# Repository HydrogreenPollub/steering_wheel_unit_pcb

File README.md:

View this project on [CADLAB.io](https://cadlab.io/project/29096). 

# steering_wheel_unit_pcb

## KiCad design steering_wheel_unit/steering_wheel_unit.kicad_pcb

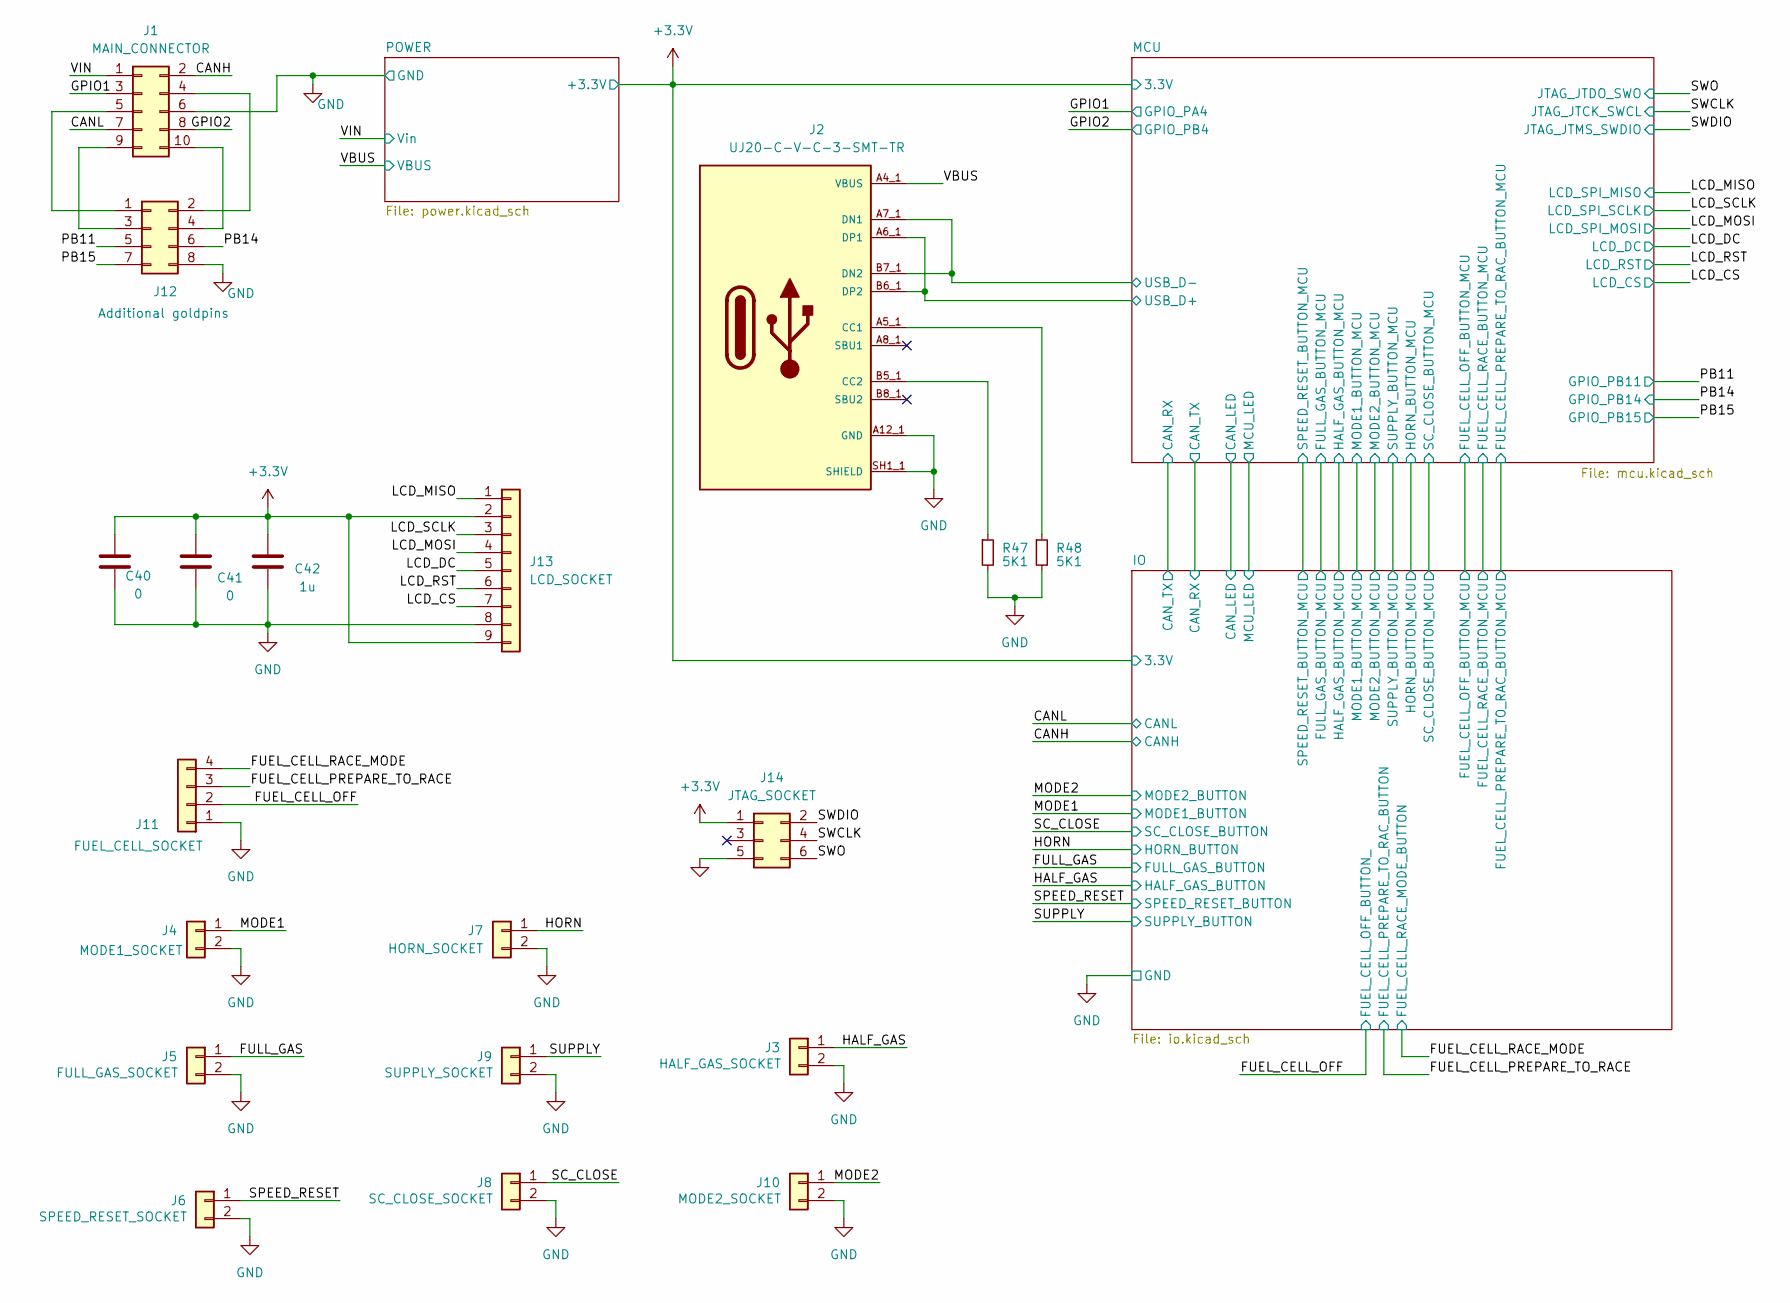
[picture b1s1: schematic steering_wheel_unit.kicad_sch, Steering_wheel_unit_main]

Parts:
C40, C41: 0; C_1206_3216Metric
C42: 1u; C_1206_3216Metric
J1: MAIN_CONNECTOR; MOLEX_39281103
J2: UJ20-C-V-C-3-SMT-TR; CUI_UJ20-C-V-C-3-SMT-TR; PARTREV 1.0
J3: HALF_GAS_SOCKET; JST_PH_B2B-PH-K_1x02_P2.00mm_Vertical
J4: MODE1_SOCKET; JST_PH_B2B-PH-K_1x02_P2.00mm_Vertical
J5: FULL_GAS_SOCKET; JST_PH_B2B-PH-K_1x02_P2.00mm_Vertical
J6: SPEED_RESET_SOCKET; JST_PH_B2B-PH-K_1x02_P2.00mm_Vertical
J7: HORN_SOCKET; JST_PH_B2B-PH-K_1x02_P2.00mm_Vertical
J8: SC_CLOSE_SOCKET; JST_PH_B2B-PH-K_1x02_P2.00mm_Vertical
J9: SUPPLY_SOCKET; JST_PH_B2B-PH-K_1x02_P2.00mm_Vertical
J10: MODE2_SOCKET; JST_PH_B2B-PH-K_1x02_P2.00mm_Vertical
J11: FUEL_CELL_SOCKET; JST_PH_B4B-PH-K_1x04_P2.00mm_Vertical
J12: Additional goldpins; PinHeader_2x04_P2.54mm_Vertical
J13: LCD_SOCKET; JST_PH_B9B-PH-K_1x09_P2.00mm_Vertical
J14: JTAG_SOCKET; IDC-Header_2x03_P2.54mm_Vertical
R47, R48: 5K1; R_1206_3216Metric

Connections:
+12V: J1.1; also elsewhere on the board
/CANH: J1.2; also elsewhere on the board
/CANL: J1.7; also elsewhere on the board
/FUEL_CELL_OFF: J11.2; also elsewhere on the board
/FUEL_CELL_PREPARE_TO_RACE: J11.3; also elsewhere on the board
/FUEL_CELL_RACE_MODE: J11.4; also elsewhere on the board
/FULL_GAS: J5.1; also elsewhere on the board
/GPIO1: J1.3; also elsewhere on the board
/GPIO2: J1.8; also elsewhere on the board
/HALF_GAS: J3.1; also elsewhere on the board
/HORN: J7.1; also elsewhere on the board
/LCD_CS: J14.7; also elsewhere on the board
/LCD_MOSI: J14.4; also elsewhere on the board
/LCD_RST: J14.6; also elsewhere on the board
/LCD_SCLK: J14.3; also elsewhere on the board
/MCU/USB_D+: J2.A6_1 (DP1), J2.A6_2 (DP1), J2.B6_1 (DP2), J2.B6_2 (DP2); also elsewhere on the board
/MCU/USB_D-: J2.A7_1 (DN1), J2.A7_2 (DN1), J2.B7_1 (DN2), J2.B7_2 (DN2); also elsewhere on the board
/MODE1: J4.1; also elsewhere on the board
/MODE2: J10.1; also elsewhere on the board
/PB11: J12.5; also elsewhere on the board
/PB14: J12.6; also elsewhere on the board
/PB15: J12.7; also elsewhere on the board
/SC_CLOSE: J8.1; also elsewhere on the board
/SPEED_RESET: J6.1; also elsewhere on the board
/SUPPLY: J9.1; also elsewhere on the board
/VBUS: J2.A4_1 (VBUS), J2.A4_2 (VBUS), J2.A9_1 (VBUS), J2.A9_2 (VBUS), J2.B4_1 (VBUS), J2.B4_2 (VBUS), J2.B9_1 (VBUS), J2.B9_2 (VBUS); also elsewhere on the board
unnamed: J1.4, J12.2
unnamed: J1.5, J12.1
unnamed: J1.9, J12.3
unnamed: J1.10, J12.4
unnamed: J2.A5_1 (CC1), J2.A5_2 (CC1), R48.1
unnamed: J2.B5_1 (CC2), J2.B5_2 (CC2), R47.1

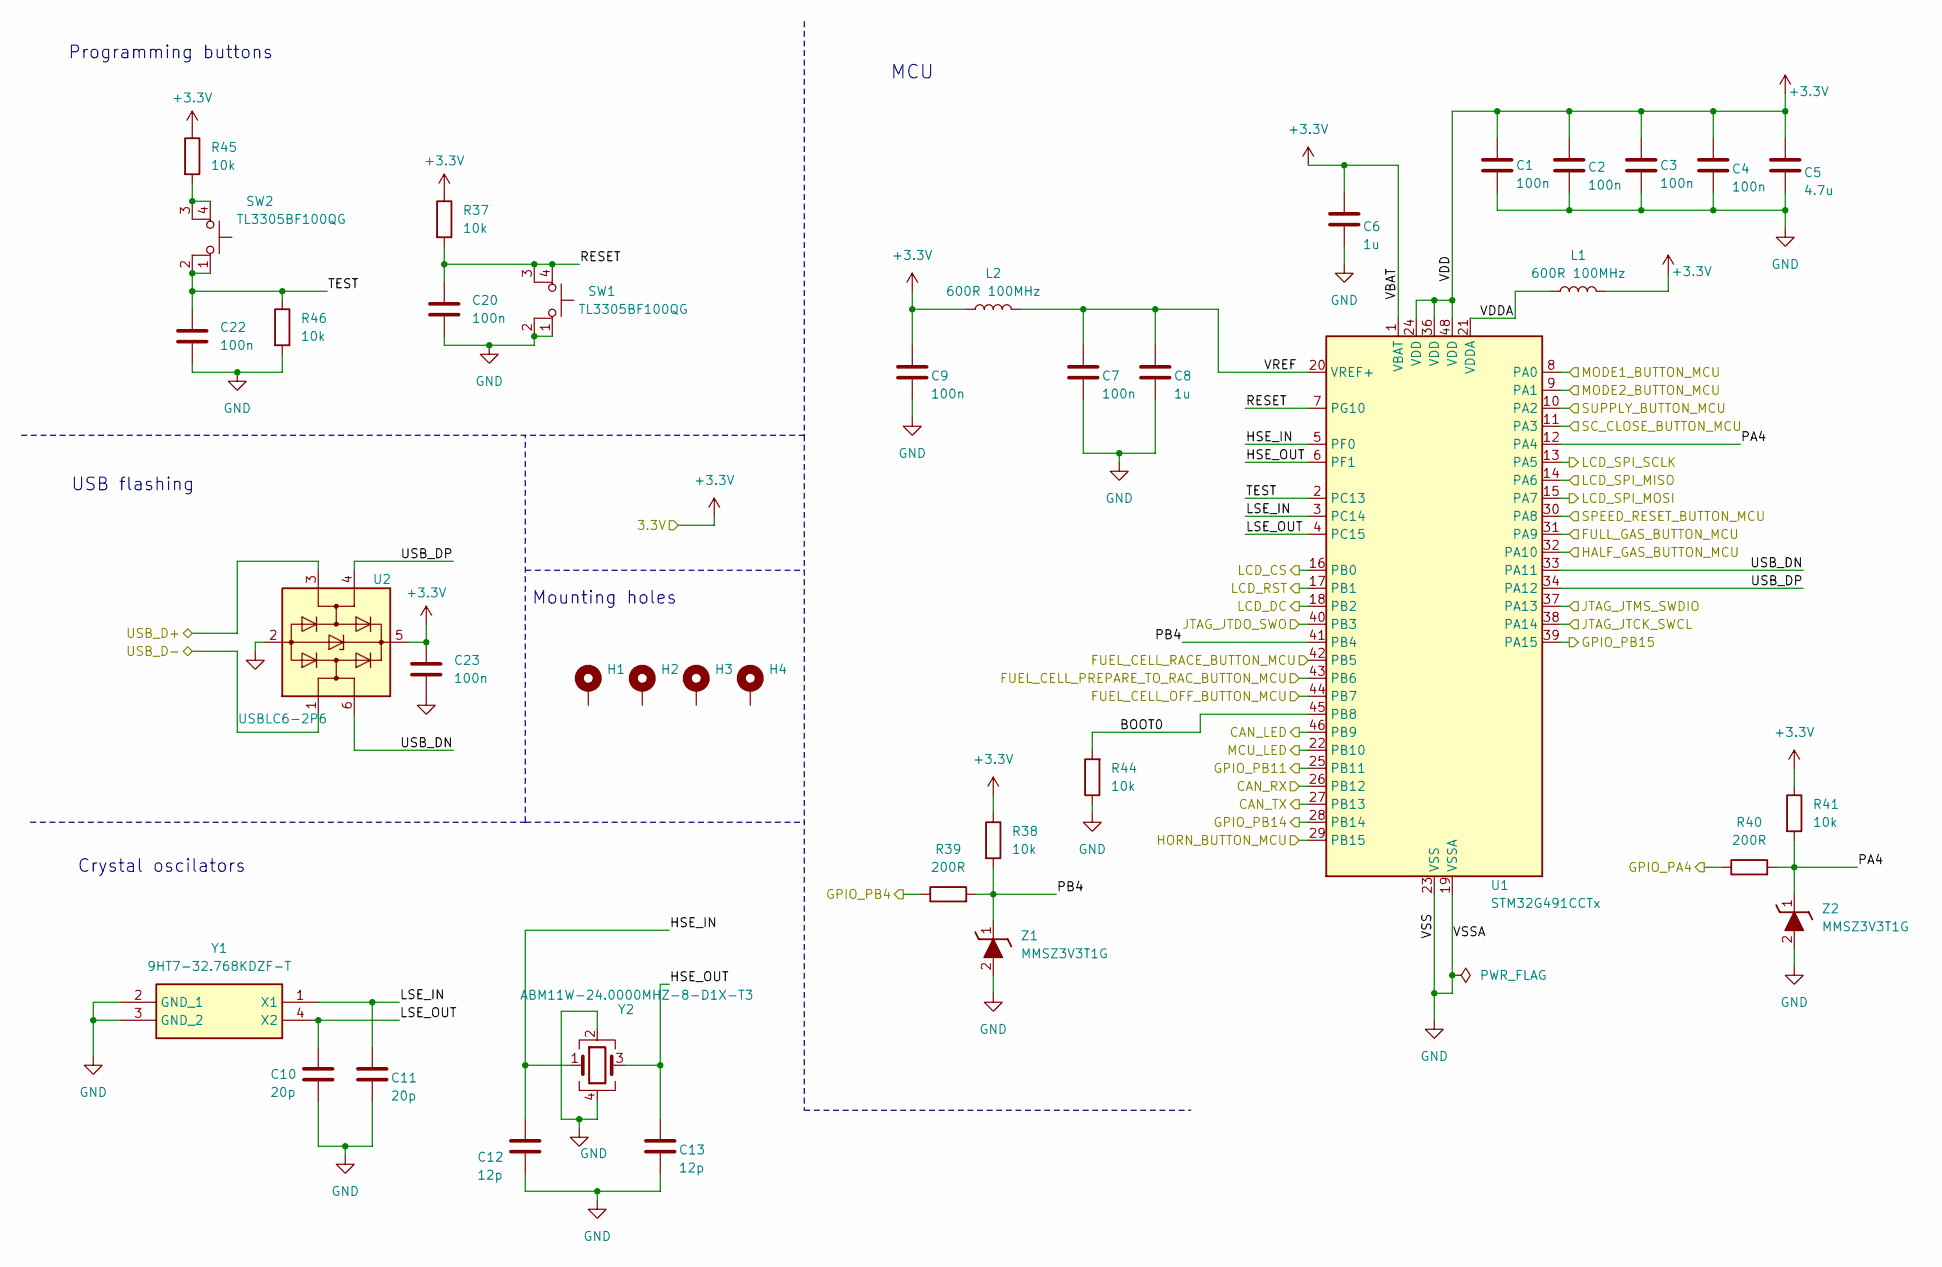
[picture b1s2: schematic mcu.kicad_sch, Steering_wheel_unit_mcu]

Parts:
C1, C2, C3, C4, C7, C9, C20, C22, C23: 100n; C_1206_3216Metric
C5: 4.7u; C_1206_3216Metric
C6, C8: 1u; C_1206_3216Metric
C10, C11: 20p; C_1206_3216Metric
C12, C13: 12p; C_1206_3216Metric
H1, H2, H3, H4: MountingHole_Pad; MountingHole_3.2mm_M3_Pad
L1, L2: 600R 100MHz; INDC1608X95N
R37, R38, R41, R44, R45, R46: 10k; R_1206_3216Metric
R39, R40: 200R; R_1206_3216Metric
SW1, SW2: TL3305BF100QG; SW_TL3305BF160QG; Mouser Part Number 612-TL3305BF100QG
U1: STM32G491CCTx; LQFP-48_7x7mm_P0.5mm
U2: USBLC6-2P6; SOT-666
Y1: 9HT7-32.768KDZF-T; 9HT732768KDZFT; Mouser Part Number 717-9HT7-32.768KDZFT
Y2: ABM11W-24.0000MHZ-8-D1X-T3; XTAL_ABM11W-24.0000MHZ-8-D1X-T3
Z1, Z2: MMSZ3V3T1G; SOD3716X135N; Mouser Part Number 863-MMSZ3V3T1G

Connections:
/GPIO1: R40.1; also elsewhere on the board
/GPIO2: R39.1; also elsewhere on the board
/IO/CAN_LED: U1.46 (PB9); also elsewhere on the board
/IO/CAN_RX: U1.27 (PB13); also elsewhere on the board
/IO/CAN_TX: U1.26 (PB12); also elsewhere on the board
/IO/FUEL_CELL_OFF_BUTTON_MCU: U1.44 (PB7); also elsewhere on the board
/IO/FUEL_CELL_PREPARE_TO_RAC_BUTTON_MCU: U1.43 (PB6); also elsewhere on the board
/IO/FUEL_CELL_RACE_BUTTON_MCU: U1.42 (PB5); also elsewhere on the board
/IO/FULL_GAS_BUTTON_MCU: U1.31 (PA9); also elsewhere on the board
/IO/HALF_GAS_BUTTON_MCU: U1.32 (PA10); also elsewhere on the board
/IO/HORN_BUTTON_MCU: U1.29 (PB15); also elsewhere on the board
/IO/MCU_LED: U1.22 (PB10); also elsewhere on the board
/IO/MODE1_BUTTON_MCU: U1.8 (PA0); also elsewhere on the board
/IO/MODE2_BUTTON_MCU: U1.9 (PA1); also elsewhere on the board
/IO/SC_CLOSE_BUTTON_MCU: U1.11 (PA3); also elsewhere on the board
/IO/SPEED_RESET_BUTTON_MCU: U1.30 (PA8); also elsewhere on the board
/IO/SUPPLY_BUTTON_MCU: U1.10 (PA2); also elsewhere on the board
/LCD_CS: U1.16 (PB0); also elsewhere on the board
/LCD_MOSI: U1.15 (PA7); also elsewhere on the board
/LCD_RST: U1.17 (PB1); also elsewhere on the board
/LCD_SCLK: U1.13 (PA5); also elsewhere on the board
/MCU/BOOT0: R44.2, U1.45 (PB8)
/MCU/HSE_IN: C12.1, U1.5 (PF0), Y2.1
/MCU/HSE_OUT: C13.1, U1.6 (PF1), Y2.3
/MCU/LSE_IN: C11.1, U1.3 (PC14), Y1.1 (X1)
/MCU/LSE_OUT: C10.1, U1.4 (PC15), Y1.4 (X2)
/MCU/PA4: R40.2, R41.2, U1.12 (PA4), Z2.1 (K); also elsewhere on the board
/MCU/RESET: C20.1, R37.2, SW1.3 (K), SW1.4 (A), U1.7 (PG10)
/MCU/TEST: C22.1, R46.1, SW2.1, SW2.2, U1.2 (PC13)
/MCU/USB_D+: U2.3 (I/O2); also elsewhere on the board
/MCU/USB_D-: U2.1 (I/O1); also elsewhere on the board
/MCU/USB_DN: U1.33 (PA11), U2.6 (I/O1)
/MCU/USB_DP: U1.34 (PA12), U2.4 (I/O2)
/MCU/VDDA: L1.1, U1.21 (VDDA)
/MCU/VREF: C7.1, C8.1, L2.2, U1.20 (VREF+)
/PB11: U1.25 (PB11); also elsewhere on the board
/PB14: U1.28 (PB14); also elsewhere on the board
/PB15: U1.39 (PA15); also elsewhere on the board
/SWCLK: U1.38 (PA14); also elsewhere on the board
/SWDIO: U1.37 (PA13); also elsewhere on the board
/SWO: U1.40 (PB3); also elsewhere on the board
unnamed: R45.2, SW2.3 (K), SW2.4 (A)

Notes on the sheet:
Mounting holes
MCU
USB flashing
Crystal oscilators
Programming buttons

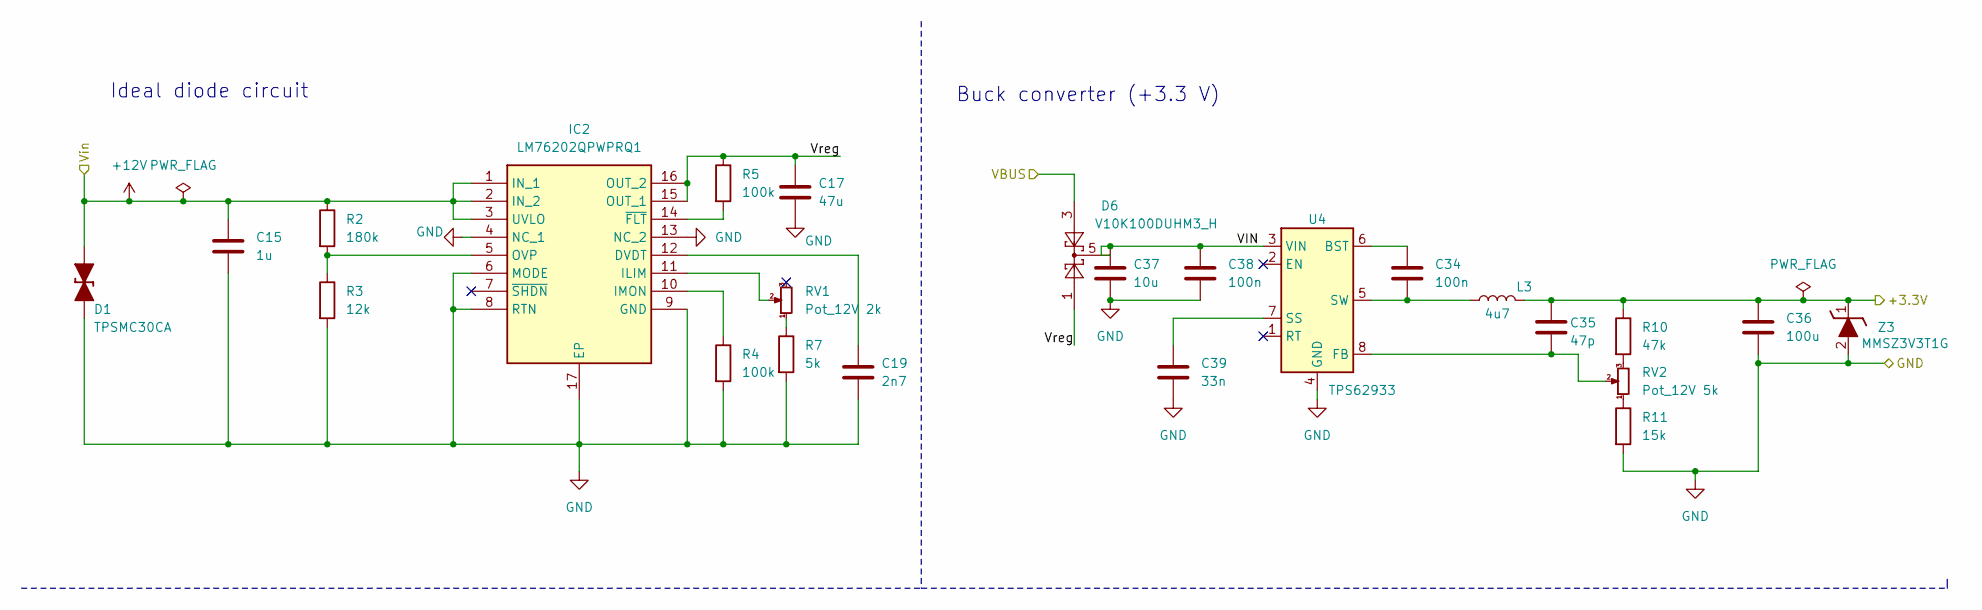
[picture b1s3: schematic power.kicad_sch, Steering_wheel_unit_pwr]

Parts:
C15: 1u; C_1206_3216Metric
C17: 47u; CP_Elec_6.3x7.7
C19: 2n7; C_1206_3216Metric
C34, C38: 100n; C_1206_3216Metric
C35: 47p; C_1206_3216Metric
C36: 100u; C_1206_3216Metric
C37: 10u; C_1206_3216Metric
C39: 33n; C_1206_3216Metric
D1: TPSMC30CA; TPSMCSeries_LTF
D6: V10K100DUHM3_H; V10K100DUHM3H; Mouser Part Number 78-V6K100DUHM3/H
IC2: LM76202QPWPRQ1; SOP65P640X120-17N; Mouser Part Number 595-LM76202QPWPRQ1
L3: 4u7; INDC1608X95N
R2: 180k; R_1206_3216Metric
R3: 12k; R_1206_3216Metric
R4, R5: 100k; R_1206_3216Metric
R7: 5k; R_1206_3216Metric
R10: 47k; R_1206_3216Metric
R11: 15k; R_1206_3216Metric
RV1: Pot_12V 2k; TC33X2503E
RV2: Pot_12V 5k; TC33X2503E
U4: TPS62933; SOTFL50P160X60-8N
Z3: MMSZ3V3T1G; SOD3716X135N; Mouser Part Number 863-MMSZ3V3T1G

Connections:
+12V: C15.1, D1.2 (A), IC2.1 (IN_1), IC2.2 (IN_2), IC2.3 (UVLO), R2.1; also elsewhere on the board
/POWER/VIN: C37.1, C38.1, D6.5, D6.6, D6.7, D6.8, U4.3 (VIN)
/POWER/Vreg: C17.1, D6.1, D6.2, IC2.15 (OUT_1), IC2.16 (OUT_2), R5.1
/VBUS: D6.3, D6.4; also elsewhere on the board
unnamed: C19.1, IC2.12 (DVDT)
unnamed: IC2.11 (ILIM), RV1.2
unnamed: IC2.10 (IMON), R4.1
unnamed: IC2.5 (OVP), R2.2, R3.1
unnamed: IC2.14 (~FLT), R5.2
unnamed: R7.1, RV1.1
unnamed: R10.2, RV2.3
unnamed: R11.1, RV2.1
unnamed: C34.1, U4.6 (BST)
unnamed: C35.2, RV2.2, U4.8 (FB)
unnamed: C39.1, U4.7 (SS)
unnamed: C34.2, L3.1, U4.5 (SW)

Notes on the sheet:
Ideal diode circuit
Buck converter (+3.3 V)

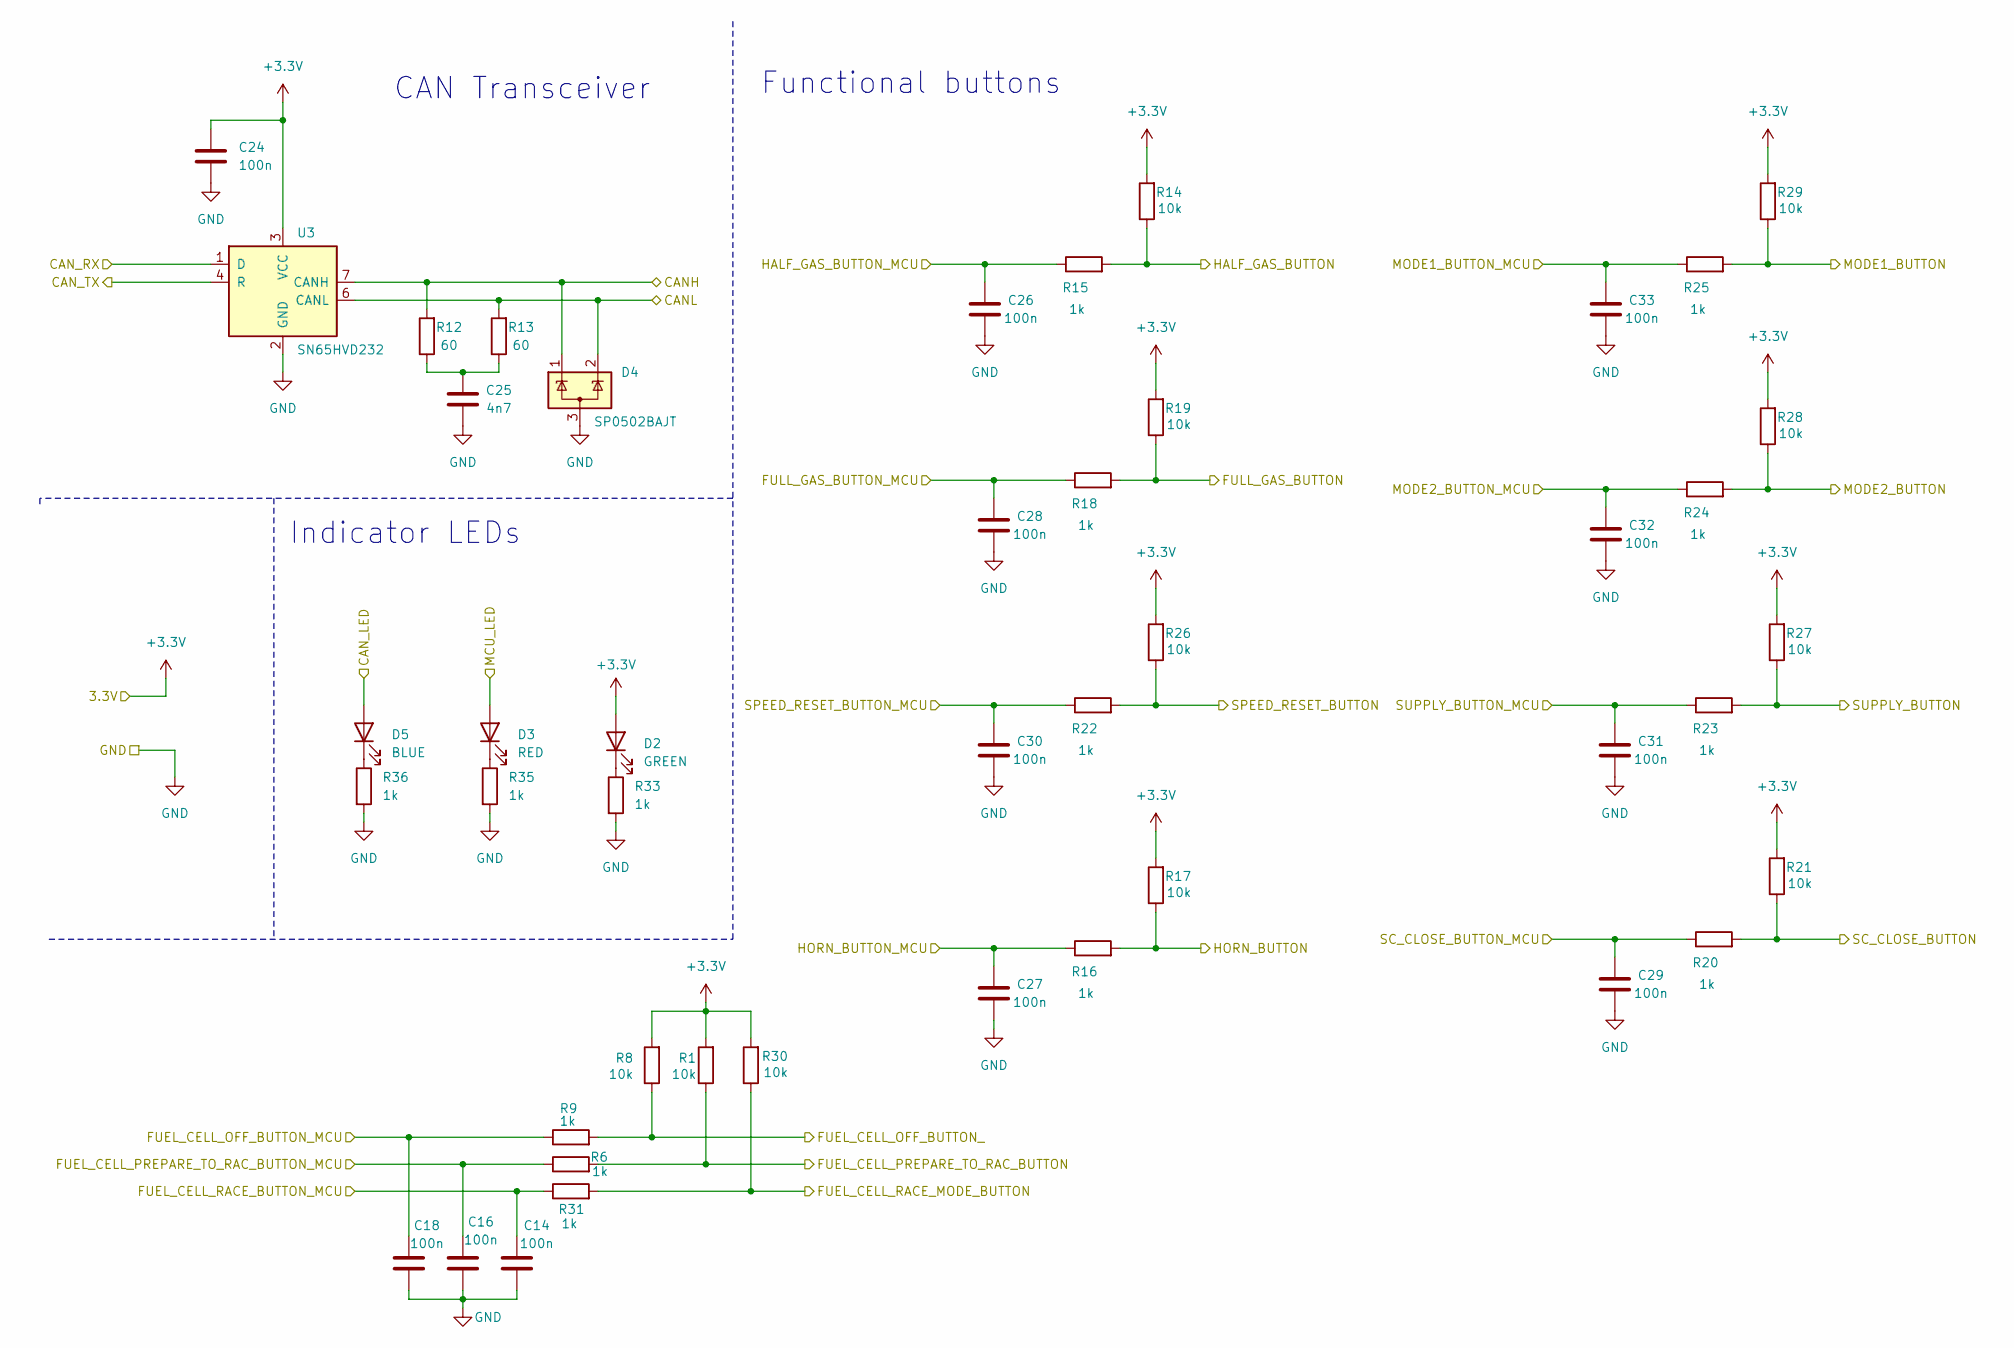
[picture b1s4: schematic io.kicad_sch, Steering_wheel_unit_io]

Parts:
C14, C16, C18, C24, C26, C27, C28, C29, C30, C31, C32, C33: 100n; C_1206_3216Metric
C25: 4n7; C_1206_3216Metric
D2: GREEN; LED_1206_3216Metric
D3: RED; LED_1206_3216Metric
D4: SP0502BAJT; SOT-323_SC-70
D5: BLUE; LED_1206_3216Metric
R1, R8, R14, R17, R19, R21, R26, R27, R28, R29, R30: 10k; R_1206_3216Metric
R6, R9, R15, R16, R18, R20, R22, R23, R24, R25, R31, R33, R35, R36: 1k; R_1206_3216Metric
R12, R13: 60; R_1206_3216Metric
U3: SN65HVD232; SOIC-8_3.9x4.9mm_P1.27mm

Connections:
/CANH: D4.1 (K), R12.2, U3.7 (CANH); also elsewhere on the board
/CANL: D4.2 (K), R13.2, U3.6 (CANL); also elsewhere on the board
/FUEL_CELL_OFF: R8.1, R9.2; also elsewhere on the board
/FUEL_CELL_PREPARE_TO_RACE: R1.1, R6.2; also elsewhere on the board
/FUEL_CELL_RACE_MODE: R30.1, R31.2; also elsewhere on the board
/FULL_GAS: R18.2, R19.1; also elsewhere on the board
/HALF_GAS: R14.1, R15.2; also elsewhere on the board
/HORN: R16.2, R17.1; also elsewhere on the board
/IO/CAN_LED: D5.2 (A); also elsewhere on the board
/IO/CAN_RX: U3.1 (D); also elsewhere on the board
/IO/CAN_TX: U3.4 (R); also elsewhere on the board
/IO/FUEL_CELL_OFF_BUTTON_MCU: C18.1, R9.1; also elsewhere on the board
/IO/FUEL_CELL_PREPARE_TO_RAC_BUTTON_MCU: C16.1, R6.1; also elsewhere on the board
/IO/FUEL_CELL_RACE_BUTTON_MCU: C14.1, R31.1; also elsewhere on the board
/IO/FULL_GAS_BUTTON_MCU: C28.1, R18.1; also elsewhere on the board
/IO/HALF_GAS_BUTTON_MCU: C26.1, R15.1; also elsewhere on the board
/IO/HORN_BUTTON_MCU: C27.1, R16.1; also elsewhere on the board
/IO/MCU_LED: D3.2 (A); also elsewhere on the board
/IO/MODE1_BUTTON_MCU: C33.1, R25.1; also elsewhere on the board
/IO/MODE2_BUTTON_MCU: C32.1, R24.1; also elsewhere on the board
/IO/SC_CLOSE_BUTTON_MCU: C29.1, R20.1; also elsewhere on the board
/IO/SPEED_RESET_BUTTON_MCU: C30.1, R22.1; also elsewhere on the board
/IO/SUPPLY_BUTTON_MCU: C31.1, R23.1; also elsewhere on the board
/MODE1: R25.2, R29.1; also elsewhere on the board
/MODE2: R24.2, R28.1; also elsewhere on the board
/SC_CLOSE: R20.2, R21.1; also elsewhere on the board
/SPEED_RESET: R22.2, R26.1; also elsewhere on the board
/SUPPLY: R23.2, R27.1; also elsewhere on the board
unnamed: C25.1, R12.1, R13.1
unnamed: D2.1 (K), R33.1
unnamed: D3.1 (K), R35.1
unnamed: D5.1 (K), R36.1

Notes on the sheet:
Functional buttons
Indicator LEDs
CAN Transceiver

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
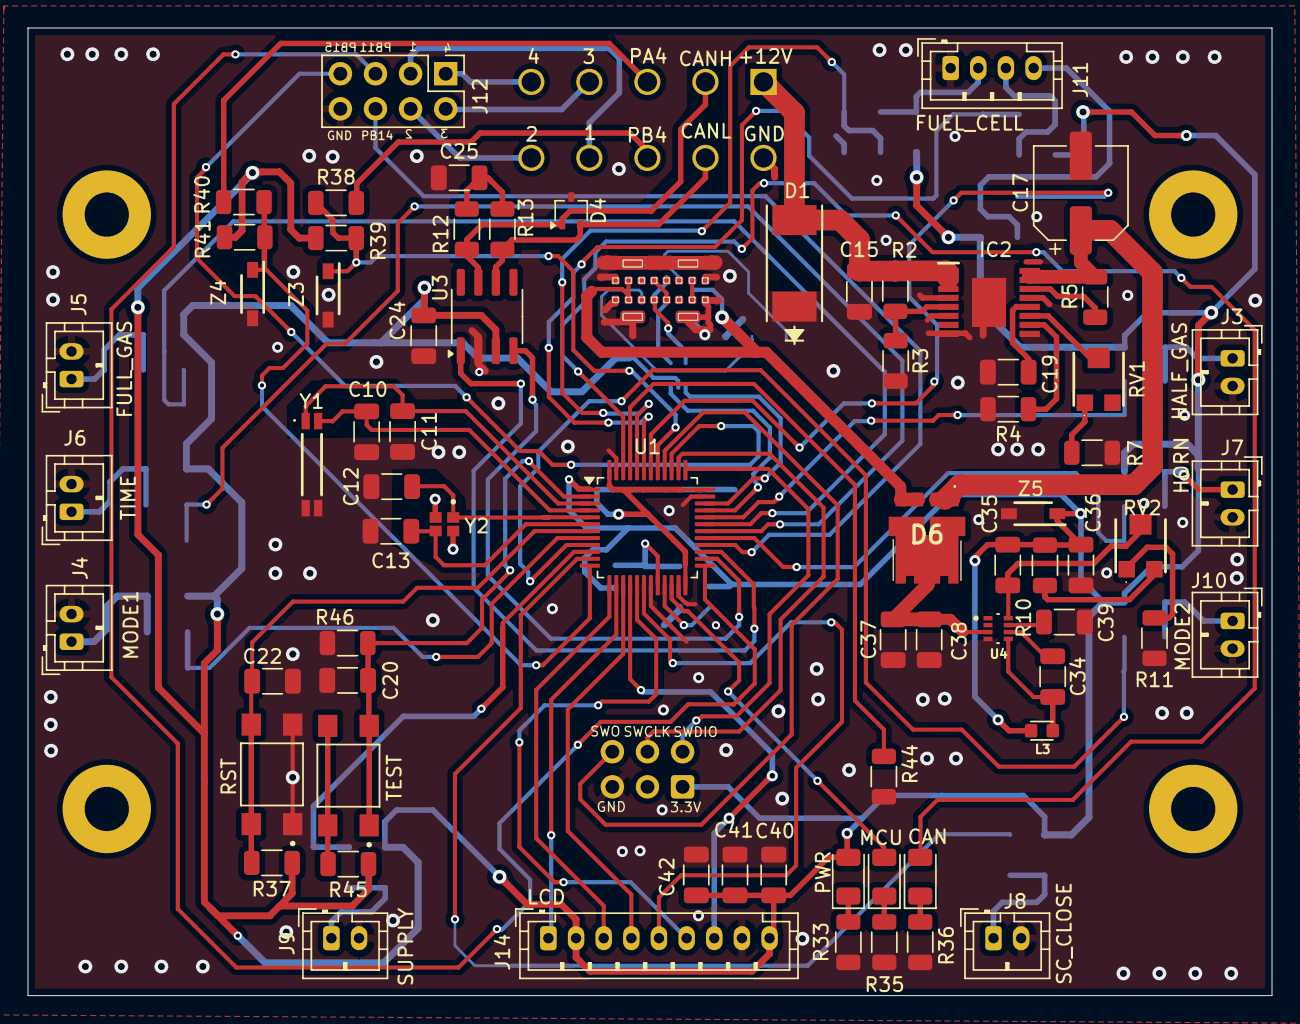
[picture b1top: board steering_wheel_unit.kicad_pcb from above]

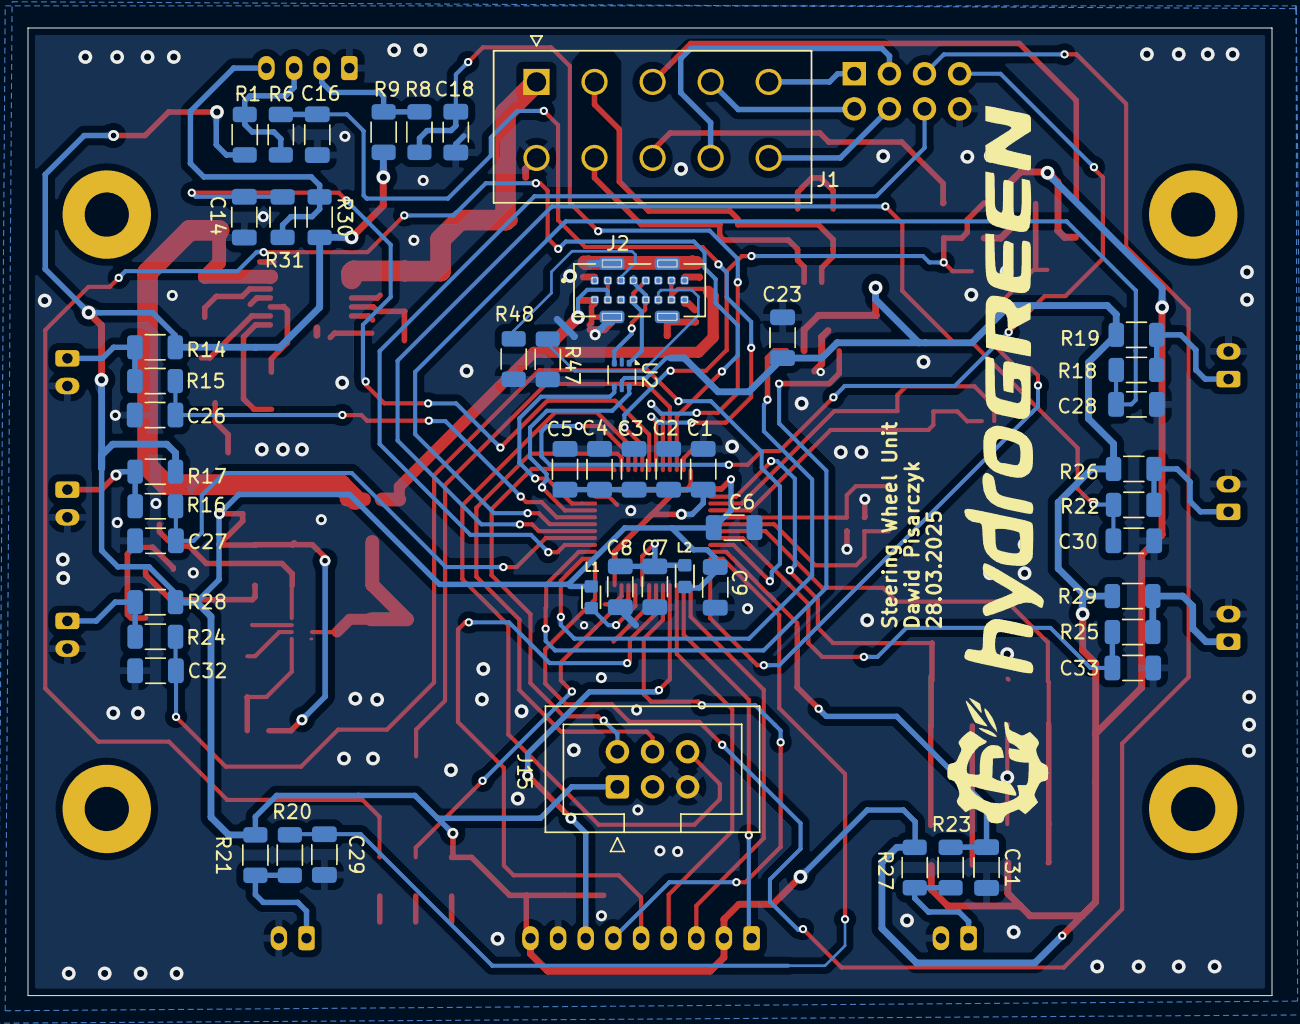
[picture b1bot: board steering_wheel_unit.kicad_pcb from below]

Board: 2 copper layers, 90.0 x 70.0 mm, 126 parts (51 on the bottom side), 86 nets.

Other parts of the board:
J15: JTAG_SOCKET; IDC-Header_2x03_P2.54mm_Vertical
Z4, Z5: MMSZ3V3T1G; SOD3716X135N

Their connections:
/MCU/PA4: Z4.1 (K); also elsewhere on the board
/SWCLK: J15.4; also elsewhere on the board
/SWDIO: J15.2; also elsewhere on the board
/SWO: J15.6; also elsewhere on the board

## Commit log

2025-03-13 add edge cuts and rough components layout
2025-03-13 organize the preliminary layout
2025-03-13 edit layout
2025-03-15 Draw part of paths
2025-03-16 Add zones for gnd and power
2025-03-17 Add some routing changes
2025-03-21 Edit tracks and add captions of elements
2025-03-24 Add dimensions
2025-03-28 Add no GND zones and logo
2025-03-29 correct captions
2025-03-31 Backlink to CADLAB.io has been added.
2025-04-02 Add more gnd vias
2025-04-03 Add manufacturing
